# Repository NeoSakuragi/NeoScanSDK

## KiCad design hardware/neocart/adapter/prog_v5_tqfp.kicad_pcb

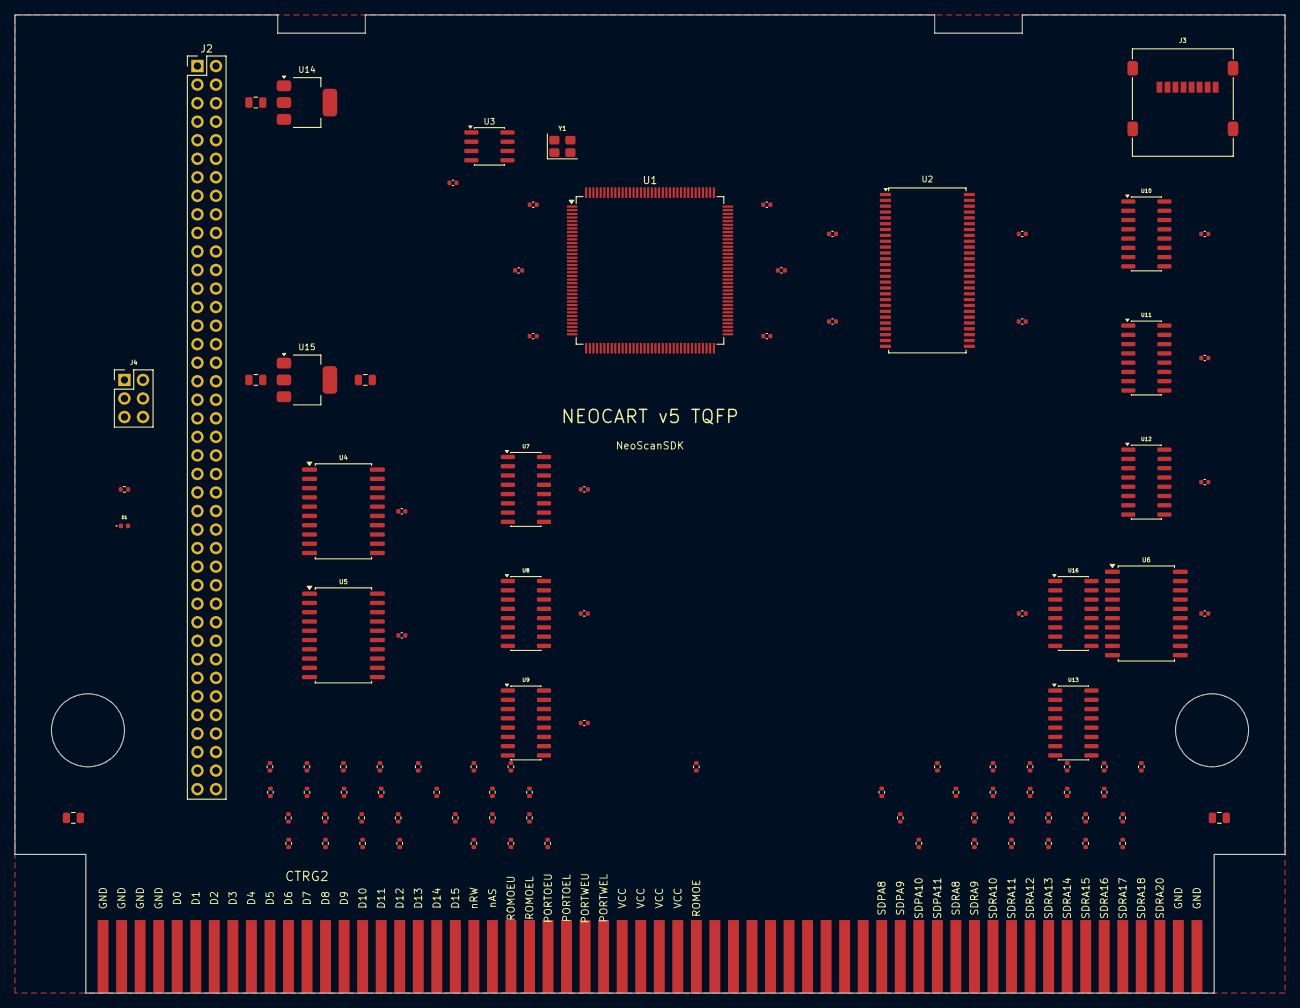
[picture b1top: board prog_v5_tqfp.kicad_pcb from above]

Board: 2 copper layers, 174.0 x 134.0 mm, 102 parts (0 on the bottom side), 241 nets, no tracks yet.

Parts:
C1, C2, C3, C4, C5, C6, C7, C8, C9, C10, C11, C12, C13, C14, C15, C16, C17, C18, C19, C20, C21: 100nF; C_0402_1005Metric
C22, C23, C24, C25, C26: 10uF; C_0805_2012Metric
CTRG2: MVS_PROG
D1: LED; LED_0402_1005Metric
J2: TO_CHA; PinHeader_2x40_P2.54mm_Vertical
J3: microSD; microSD_HC_Molex_47219-2001
J4: JTAG; PinHeader_2x03_P2.54mm_Vertical
R1, R2, R3, R4, R5, R6, R7, R8, R9, R10, R11, R12, R13, R14, R15, R16, R17, R18, R19, R20, R21, R22, R23, R24, R25, R26, R27, R28, R29, R30, R31, R32, R33, R34, R35, R36, R37, R38, R39, R40, R41, R42, R43, R44, R45, R46, R47, R48, R49, R50, R51, R52, R53: 470R; R_0402_1005Metric
R54: 1K; R_0402_1005Metric
U1: LFE5U-25F; TQFP-144_20x20mm_P0.5mm
U2: W9825G6KH; TSOP-II-54_22.2x10.16mm_P0.8mm
U3: W25Q32; SOIC-8_3.9x4.9mm_P1.27mm
U4, U5, U6: 74LVC245; SOIC-20W_7.5x12.8mm_P1.27mm
U7, U8, U9, U10, U11, U12, U13: 74HC165; SOIC-16_3.9x9.9mm_P1.27mm
U14: AMS1117-3.3; SOT-223-3_TabPin2
U15: AMS1117-1.2; SOT-223-3_TabPin2
U16: 74HC595; SOIC-16_3.9x9.9mm_P1.27mm
Y1: 50MHz; Crystal_SMD_3225-4Pin_3.2x2.5mm

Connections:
68KCLK: CTRG2.B24, R25.1
A1: CTRG2.B5, R1.1
A1_R: R1.2, U7.7
A2: CTRG2.B6, R2.1
A2_R: R2.2, U7.6
A3: CTRG2.B7, R3.1
A3_R: R3.2, U7.5
A4: CTRG2.B8, R4.1
A4_R: R4.2, U7.4
A5: CTRG2.B9, R5.1
A5_R: R5.2, U7.3
A6: CTRG2.B10, R6.1
A6_R: R6.2, U7.13
A7: CTRG2.B11, R7.1
A7_R: R7.2, U7.12
A8: CTRG2.B12, R8.1
A8_R: R8.2, U7.11
A9: CTRG2.B13, R9.1
A9_R: R9.2, U8.7
A10: CTRG2.B14, R10.1
A10_R: R10.2, U8.6
A11: CTRG2.B15, R11.1
A11_R: R11.2, U8.5
A12: CTRG2.B16, R12.1
A12_R: R12.2, U8.4
A13: CTRG2.B17, R13.1
A13_R: R13.2, U8.3
A14: CTRG2.B18, R14.1
A14_R: R14.2, U8.13
A15: CTRG2.B19, R15.1
A15_R: R15.2, U8.12
A16: CTRG2.B20, R16.1
A16_R: R16.2, U8.11
A17: CTRG2.B21, R17.1
A17_R: R17.2, U9.7
A18: CTRG2.B22, R18.1
A18_R: R18.2, U9.6
A19: CTRG2.B23, R19.1
A19_R: R19.2, U9.5
BUF_OE: U1.124, U4.19, U5.19
BUS_DIR: U1.121, U4.1, U5.1
CHA_CA4: J2.24, U1.12
CLK24M: J2.23, U1.3
CLK68K_DIV: R25.2, R26.1
CLK_C: J2.10, U1.116
CLK_CR: J2.16, U1.5
CLK_S: J2.13, U1.119
CLK_SF: J2.19, U1.10
CLK_SOUT: U1.49, U16.11
CLK_SR: U1.133, U7.2, U8.2, U9.2, U10.2, U11.2, U12.2, U13.2
D0: CTRG2.A5, U4.2
D1: CTRG2.A6, U4.3
D2: CTRG2.A7, U4.4
D3: CTRG2.A8, U4.5
D4: CTRG2.A9, U4.6
D5: CTRG2.A10, U4.7
D6: CTRG2.A11, U4.8
D7: CTRG2.A12, U4.9
D8: CTRG2.A13, U5.2
D9: CTRG2.A14, U5.3
D10: CTRG2.A15, U5.4
D11: CTRG2.A16, U5.5
D12: CTRG2.A17, U5.6
D13: CTRG2.A18, U5.7
D14: CTRG2.A19, U5.8
D15: CTRG2.A20, U5.9
FD0: U1.18, U4.18
FD1: U1.19, U4.17
FD2: U1.22, U4.16
FD3: U1.23, U4.15
FD4: U1.24, U4.14
FD5: U1.25, U4.13
FD6: U1.26, U4.12
FD7: U1.27, U4.11
FD8: U1.28, U5.18
FD9: U1.30, U5.17
FD10: U1.31, U5.16
FD11: U1.33, U5.15
FD12: U1.34, U5.14
FD13: U1.35, U5.13
FD14: U1.37, U5.12
FD15: U1.140, U5.11
FLASH_CLK: U1.54, U3.6
FLASH_CS: U1.48, U3.1
FLASH_MISO: U1.46, U3.2
FLASH_MOSI: U1.47, U3.5
FSD0: U6.2, U16.15
FSD1: U6.3, U16.1
FSD2: U6.4, U16.2
FSD3: U6.5, U16.3
FSD4: U6.6, U16.4
FSD5: U6.7, U16.5
FSD6: U6.8, U16.6
FSD7: U6.9, U16.7
GND: C1.2, C2.2, C3.2, C4.2, C5.2, C6.2, C7.2, C8.2, C9.2, C10.2, C11.2, C12.2, C13.2, C14.2, C15.2, C16.2, C17.2, C18.2, C19.2, C20.2, C21.2, C22.2, C23.2, C24.2, C25.2, C26.2, CTRG2.A1, CTRG2.A2, CTRG2.A3, CTRG2.A4, CTRG2.A59, CTRG2.A60, CTRG2.B1, CTRG2.B2, CTRG2.B3, CTRG2.B4, CTRG2.B26, CTRG2.B27, CTRG2.B59, CTRG2.B60, D1.2, J2.5, J2.6, J2.7, J2.8, J2.29, J2.30, J2.31, J2.32, J2.33, J2.34, J2.35, J2.36, J2.37, J2.38, J2.39, J2.40, J2.41, J2.42, J2.43, J2.44, J2.45, J2.46, J2.47, J2.48, J2.49, J2.50, J2.51, J2.52, J2.53, J2.54, J2.55, J2.56, J2.57, J2.58, J2.59, J2.60, J2.61, J2.62, J2.63, J2.64, J2.65, J2.66, J2.67, J2.68, J2.69, J2.70, J2.71, J2.72, J2.73, J2.74, J2.75, J2.76, J2.77, J2.78, J2.79, J2.80, J3.3, J3.6, J3.9, J4.6, R26.2, U1.8, U1.15, U1.21, U1.32, U1.42, U1.65, U1.75, U1.85, U1.87, U1.101, U1.123, U1.129, U1.131, U1.138, U2.3, U2.6, U2.9, U2.12, U2.39, U2.43, U2.46, U2.49, U2.52, U3.4, U4.10, U5.10, U6.10, U6.19, U7.8, U7.10, U7.14, U8.8, U8.14, U9.8, U9.14, U10.8, U10.10, U10.14, U11.8, U11.14, U12.8, U12.14, U13.3, U13.4, U13.8, U13.11, U13.12, U13.13, U13.14, U14.1, U15.1, U16.8, U16.13, Y1.3
JTAG_TCK: J4.3, U1.63
JTAG_TDI: J4.5, U1.61
JTAG_TDO: J4.4, U1.60
JTAG_TMS: J4.2, U1.64
LATCH_CR: J2.17, U1.6
LATCH_SF: J2.20, U1.11
LATCH_SOUT: U1.50, U16.12
LED1: D1.1, R54.1, U1.51
LOAD_C: J2.11, U1.117
LOAD_S: J2.14, U1.120
LOAD_SR: U1.134, U7.1, U8.1, U9.1, U10.1, U11.1, U12.1, U13.1
PCK1B: J2.21, U1.1
PCK2B: J2.22, U1.2
RESET_CHA: J2.27, U1.126
ROMOE: CTRG2.A33, R24.1
ROMOEL: CTRG2.A24, R23.1
ROMOEL_R: R23.2, U9.12
ROMOEU: CTRG2.A23, R22.1
ROMOEU_R: R22.2, U9.13
ROMOE_R: R24.2, U9.11
SDMRD: CTRG2.B58, R52.1
SDMRD_CHA: J2.25, U1.13
SDMRD_R: R52.2, U13.6
SDPA8: CTRG2.A43, R48.1
SDPA8_R: R48.2, U12.13
SDPA9: CTRG2.A44, R49.1
SDPA9_R: R49.2, U12.12
SDPA10: CTRG2.A45, R50.1
SDPA10_R: R50.2, U12.11
SDPA11: CTRG2.A46, R51.1
SDPA11_R: R51.2, U13.7
SDPAD0: CTRG2.B40, U6.18
SDPAD1: CTRG2.B41, U6.17
SDPAD2: CTRG2.B42, U6.16
SDPAD3: CTRG2.B43, U6.15
SDPAD4: CTRG2.B44, U6.14
SDPAD5: CTRG2.B45, U6.13
SDPAD6: CTRG2.B46, U6.12
SDPAD7: CTRG2.B47, U6.11
SDRA0: CTRG2.B48, R27.1
SDRA0_R: R27.2, U10.7
SDRA1: CTRG2.B49, R28.1
SDRA1_R: R28.2, U10.6
SDRA2: CTRG2.B50, R29.1
SDRA2_R: R29.2, U10.5
SDRA3: CTRG2.B51, R30.1
SDRA3_R: R30.2, U10.4
SDRA4: CTRG2.B52, R31.1
SDRA4_R: R31.2, U10.3
SDRA5: CTRG2.B53, R32.1
SDRA5_R: R32.2, U10.13
SDRA6: CTRG2.B54, R33.1
SDRA6_R: R33.2, U10.12
SDRA7: CTRG2.B55, R34.1
SDRA7_R: R34.2, U10.11
SDRA8: CTRG2.A47, R35.1
SDRA8_R: R35.2, U11.7
SDRA9: CTRG2.A48, R36.1
SDRA9_R: R36.2, U11.6
SDRA10: CTRG2.A49, R37.1
SDRA10_R: R37.2, U11.5
SDRA11: CTRG2.A50, R38.1
SDRA11_R: R38.2, U11.4
SDRA12: CTRG2.A51, R39.1
SDRA12_R: R39.2, U11.3
SDRA13: CTRG2.A52, R40.1
SDRA13_R: R40.2, U11.13
SDRA14: CTRG2.A53, R41.1
SDRA14_R: R41.2, U11.12
SDRA15: CTRG2.A54, R42.1
SDRA15_R: R42.2, U11.11
SDRA16: CTRG2.A55, R43.1
SDRA16_R: R43.2, U12.7
SDRA17: CTRG2.A56, R44.1
SDRA17_R: R44.2, U12.6
SDRA18: CTRG2.A57, R45.1
SDRA18_R: R45.2, U12.5
SDRA19: CTRG2.B57, R46.1
SDRA19_R: R46.2, U12.4
SDRA20: CTRG2.A58, R47.1
SDRA20_R: R47.2, U12.3
SDRAM_A0: U1.67, U2.23
SDRAM_A1: U1.68, U2.24
SDRAM_A2: U1.69, U2.25
SDRAM_A3: U1.71, U2.26
SDRAM_A4: U1.72, U2.29
SDRAM_A5: U1.73, U2.30
SDRAM_A6: U1.74, U2.31
SDRAM_A7: U1.76, U2.32
SDRAM_A8: U1.77, U2.33
SDRAM_A9: U1.78, U2.34
SDRAM_A10: U1.79, U2.22
SDRAM_A11: U1.80, U2.35
SDRAM_A12: U1.81, U2.36
SDRAM_BA0: U1.82, U2.20
SDRAM_BA1: U1.84, U2.21
SDRAM_CAS: U1.113, U2.17
SDRAM_CKE: U1.110, U2.37
SDRAM_CLK: U1.107, U2.38
SDRAM_CS: U1.111, U2.19
SDRAM_D0: U1.88, U2.2
SDRAM_D1: U1.89, U2.4
SDRAM_D2: U1.90, U2.5
SDRAM_D3: U1.91, U2.7
SDRAM_D4: U1.92, U2.8
SDRAM_D5: U1.93, U2.10
SDRAM_D6: U1.94, U2.11
SDRAM_D7: U1.95, U2.13
SDRAM_D8: U1.97, U2.42
SDRAM_D9: U1.98, U2.44
SDRAM_D10: U1.99, U2.45
SDRAM_D11: U1.102, U2.47
SDRAM_D12: U1.103, U2.48
SDRAM_D13: U1.104, U2.50
SDRAM_D14: U1.105, U2.51
SDRAM_D15: U1.106, U2.53
SDRAM_DQM: U1.108, U2.15
SDRAM_RAS: U1.112, U2.18
SDRAM_WE: U1.114, U2.16
SDROE: CTRG2.B56, R53.1
SDROE_R: R53.2, U13.5
SDROM: J2.26, U1.14
SD_CLK: J3.5, U1.40
SD_CS: J3.1, U1.39
SD_MISO: J3.7, U1.44
SD_MOSI: J3.2, U1.41
SER_C: J2.9, U1.115
SER_CR: J2.15, U1.4
SER_P: U1.125, U9.9
SER_S: J2.12, U1.118
SER_SD: U1.141, U13.9
SER_SF: J2.18, U1.7
SER_SOUT: U1.45, U16.14
SR1_OUT: U7.9, U8.10
SR2_OUT: U8.9, U9.10
SSR1_OUT: U10.9, U11.10
SSR2_OUT: U11.9, U12.10
SSR3_OUT: U12.9, U13.10
SYSTEMB: J2.28, U1.127
VCC_1V1: C1.1, C2.1, C3.1, C4.1, C25.1, U1.20, U1.29, U1.38, U1.66, U1.83, U1.130, U15.2
VCC_3V3: C5.1, C6.1, C7.1, C8.1, C9.1, C10.1, C11.1, C21.1, C23.1, C24.1, J2.1, J2.2, J3.4, J4.1, R54.2, U1.9, U1.16, U1.17, U1.36, U1.43, U1.53, U1.70, U1.86, U1.96, U1.100, U1.122, U1.132, U1.137, U2.1, U2.14, U2.27, U2.28, U2.40, U2.41, U2.54, U3.3, U3.7, U3.8, U14.2, U15.3, U16.10, U16.16
VCC_5V: C12.1, C13.1, C14.1, C15.1, C16.1, C17.1, C18.1, C19.1, C20.1, C22.1, C26.1, CTRG2.A29, CTRG2.A30, CTRG2.A31, CTRG2.A32, CTRG2.B29, CTRG2.B30, CTRG2.B31, CTRG2.B32, J2.3, J2.4, U4.20, U5.20, U6.1, U6.20, U7.16, U8.16, U9.16, U10.16, U11.16, U12.16, U13.16, U14.3
nAS: CTRG2.A22, R21.1
nAS_R: R21.2, U9.3
nRW: CTRG2.A21, R20.1
nRW_R: R20.2, U9.4

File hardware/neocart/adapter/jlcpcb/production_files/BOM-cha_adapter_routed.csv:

Comment,Designator,Footprint,LCSC,Quantity
100nF,"C1,C2,C3,C4,C5",C_0402_1005Metric,C1525,5
10uF,C6,C_0805_2012Metric,C15850,1
470R,"R1,R10,R11,R12,R13,R14,R15,R16,R17,R18,R19,R2,R20,R21,R22,R23,R24,R25,R26,R27,R28,R29,R3,R30,R31,R32,R33,R34,R35,R36,R37,R38,R39,R4,R40,R5,R6,R7,R8,R9",R_0402_1005Metric,C25900,40
74HC165,"U1,U2,U3,U4,U5",SOIC-16_3.9x9.9mm_P1.27mm,C5613,5
FROM_PROG,J2,PinHeader_2x40_P2.54mm_Vertical,C5224034,1

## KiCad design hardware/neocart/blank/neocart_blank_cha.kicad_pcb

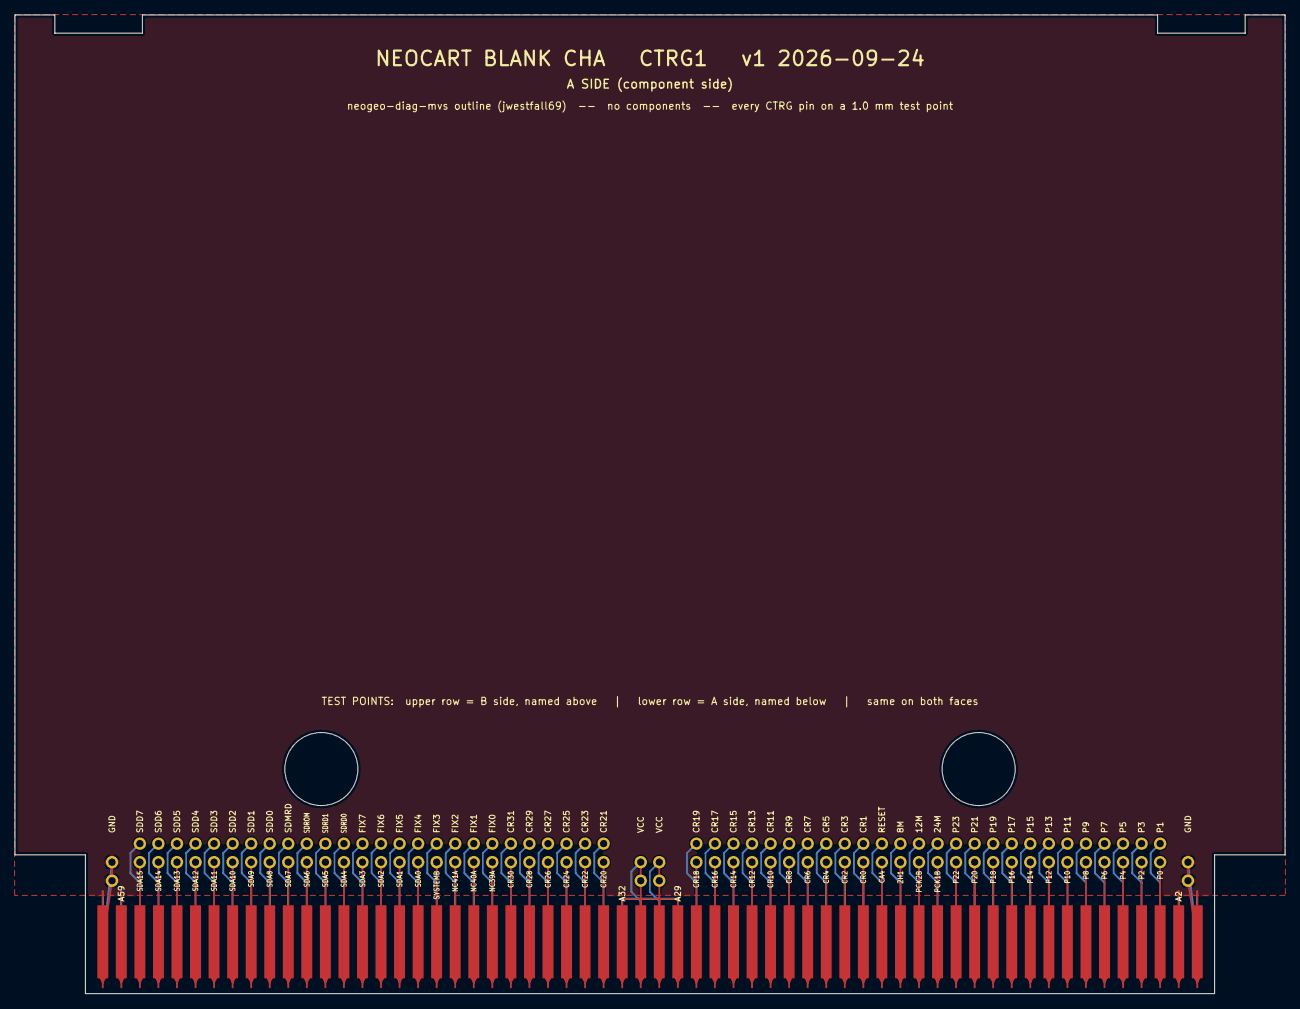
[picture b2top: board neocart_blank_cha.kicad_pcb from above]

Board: 2 copper layers, 173.9 x 134.0 mm, 4 parts (1 on the bottom side), 106 nets.

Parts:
J1: neogeo-mvs-cha-a-side-edge; neogeo-mvs-a-side-edge
J2: neogeo-mvs-cha-a-side-edge; neogeo-mvs-cha-edge-test-points
J3: neogeo-mvs-cha-b-side-edge; neogeo-mvs-cha-edge-test-points
J4: neogeo-mvs-cha-b-side-edge; neogeo-mvs-b-side-edge

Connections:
2H1: J1.17 (2H1), J2.17 (2H1)
8M: J3.17 (8M), J4.17 (8M)
12M: J3.16 (12M), J4.16 (12M)
24M: J3.15 (24M), J4.15 (24M)
CA4: J1.18 (CA4), J2.18 (CA4)
CR0: J1.19 (CR0), J2.19 (CR0)
CR1: J3.19 (CR1), J4.19 (CR1)
CR2: J1.20 (CR2), J2.20 (CR2)
CR3: J3.20 (CR3), J4.20 (CR3)
CR4: J1.21 (CR4), J2.21 (CR4)
CR5: J3.21 (CR5), J4.21 (CR5)
CR6: J1.22 (CR6), J2.22 (CR6)
CR7: J3.22 (CR7), J4.22 (CR7)
CR8: J1.23 (CR8), J2.23 (CR8)
CR9: J3.23 (CR9), J4.23 (CR9)
CR10: J1.24 (CR10), J2.24 (CR10)
CR11: J3.24 (CR11), J4.24 (CR11)
CR12: J1.25 (CR12), J2.25 (CR12)
CR13: J3.25 (CR13), J4.25 (CR13)
CR14: J1.26 (CR14), J2.26 (CR14)
CR15: J3.26 (CR15), J4.26 (CR15)
CR16: J1.27 (CR16), J2.27 (CR16)
CR17: J3.27 (CR17), J4.27 (CR17)
CR18: J1.28 (CR18), J2.28 (CR18)
CR19: J3.28 (CR19), J4.28 (CR19)
CR20: J1.33 (CR20), J2.33 (CR20)
CR21: J3.33 (CR21), J4.33 (CR21)
CR22: J1.34 (CR22), J2.34 (CR22)
CR23: J3.34 (CR23), J4.34 (CR23)
CR24: J1.35 (CR24), J2.35 (CR24)
CR25: J3.35 (CR25), J4.35 (CR25)
CR26: J1.36 (CR26), J2.36 (CR26)
CR27: J3.36 (CR27), J4.36 (CR27)
CR28: J1.37 (CR28), J2.37 (CR28)
CR29: J3.37 (CR29), J4.37 (CR29)
CR30: J1.38 (CR30), J2.38 (CR30)
CR31: J3.38 (CR31), J4.38 (CR31)
FIX0: J3.39 (FIXD0), J4.39 (FIXD0)
FIX1: J3.40 (FIXD1), J4.40 (FIXD1)
FIX2: J3.41 (FIXD2), J4.41 (FIXD2)
FIX3: J3.42 (FIXD3), J4.42 (FIXD3)
FIX4: J3.43 (FIXD4), J4.43 (FIXD4)
FIX5: J3.44 (FIXD5), J4.44 (FIXD5)
FIX6: J3.45 (FIXD6), J4.45 (FIXD6)
FIX7: J3.46 (FIXD7), J4.46 (FIXD7)
GND: J1.1 (GND), J1.2 (GND), J1.59 (GND), J1.60 (GND), J2.1 (GND), J2.60 (GND), J3.1 (GND), J3.60 (GND), J4.1 (GND), J4.2 (GND), J4.59 (GND), J4.60 (GND)
NC39A: J1.39 (NC), J2.39 (NC)
NC40A: J1.40 (NC), J2.40 (NC)
NC41A: J1.41 (NC), J2.41 (NC)
P0: J1.3 (P0), J2.3 (P0)
P1: J3.3 (P1), J4.3 (P1)
P2: J1.4 (P2), J2.4 (P2)
P3: J3.4 (P3), J4.4 (P3)
P4: J1.5 (P4), J2.5 (P4)
P5: J3.5, J4.5
P6: J1.6, J2.6
P7: J3.6 (P7), J4.6 (P7)
P8: J1.7 (P8), J2.7 (P8)
P9: J3.7 (P9), J4.7 (P9)
P10: J1.8 (P10), J2.8 (P10)
P11: J3.8 (P11), J4.8 (P11)
P12: J1.9 (P12), J2.9 (P12)
P13: J3.9 (P13), J4.9 (P13)
P14: J1.10 (P14), J2.10 (P14)
P15: J3.10 (P15), J4.10 (P15)
P16: J1.11 (P16), J2.11 (P16)
P17: J3.11 (P17), J4.11 (P17)
P18: J1.12 (P18), J2.12 (P18)
P19: J3.12 (P19), J4.12 (P19)
P20: J1.13 (P20), J2.13 (P20)
P21: J3.13 (P21), J4.13 (P21)
P22: J1.14 (P22), J2.14 (P22)
P23: J3.14 (P23), J4.14 (P23)
PCK1B: J1.15 (PCK1B), J2.15 (PCK1B)
PCK2B: J1.16 (PCK2B), J2.16 (PCK2B)
RESET: J3.18 (RESET), J4.18 (RESET)
SDA0: J1.43 (SDA0), J2.43 (SDA0)
SDA1: J1.44 (SDA1), J2.44 (SDA1)
SDA2: J1.45 (SDA2), J2.45 (SDA2)
SDA3: J1.46 (SDA3), J2.46 (SDA3)
SDA4: J1.47 (SDA4), J2.47 (SDA4)
SDA5: J1.48 (SDA5), J2.48 (SDA5)
SDA6: J1.49 (SDA6), J2.49 (SDA6)
SDA7: J1.50 (SDA7), J2.50 (SDA7)
SDA8: J1.51 (SDA8), J2.51 (SDA8)
SDA9: J1.52 (SDA9), J2.52 (SDA9)
SDA10: J1.53 (SDA10), J2.53 (SDA10)
SDA11: J1.54 (SDA11), J2.54 (SDA11)
SDA12: J1.55 (SDA12), J2.55 (SDA12)
SDA13: J1.56 (SDA13), J2.56 (SDA13)
SDA14: J1.57 (SDA14), J2.57 (SDA14)
SDA15: J1.58 (SDA15), J2.58 (SDA15)
SDD0: J3.51 (SDD0), J4.51 (SDD0)
SDD1: J3.52 (SDD1), J4.52 (SDD1)
SDD2: J3.53 (SDD2), J4.53 (SDD2)
SDD3: J3.54 (SDD3), J4.54 (SDD3)
SDD4: J3.55 (SDD4), J4.55 (SDD4)
SDD5: J3.56 (SDD5), J4.56 (SDD5)
SDD6: J3.57 (SDD6), J4.57 (SDD6)
SDD7: J3.58 (SDD7), J4.58 (SDD7)
SDMRD: J3.50 (SDMRD), J4.50 (SDMRD)
SDRD0: J3.47 (SDRD0), J4.47 (SDRD0)
SDRD1: J3.48 (SDRD1), J4.48 (SDRD1)
SDROM: J3.49 (SDROM), J4.49 (SDROM)
SYSTEMB: J1.42 (SLOTCS), J2.42 (SLOTCS)
VCC: J1.29 (VCC), J1.30 (VCC), J1.31 (VCC), J1.32 (VCC), J2.30 (VCC), J2.31 (VCC), J3.30 (VCC), J3.31 (VCC), J4.29 (VCC), J4.30 (VCC), J4.31 (VCC), J4.32 (VCC)

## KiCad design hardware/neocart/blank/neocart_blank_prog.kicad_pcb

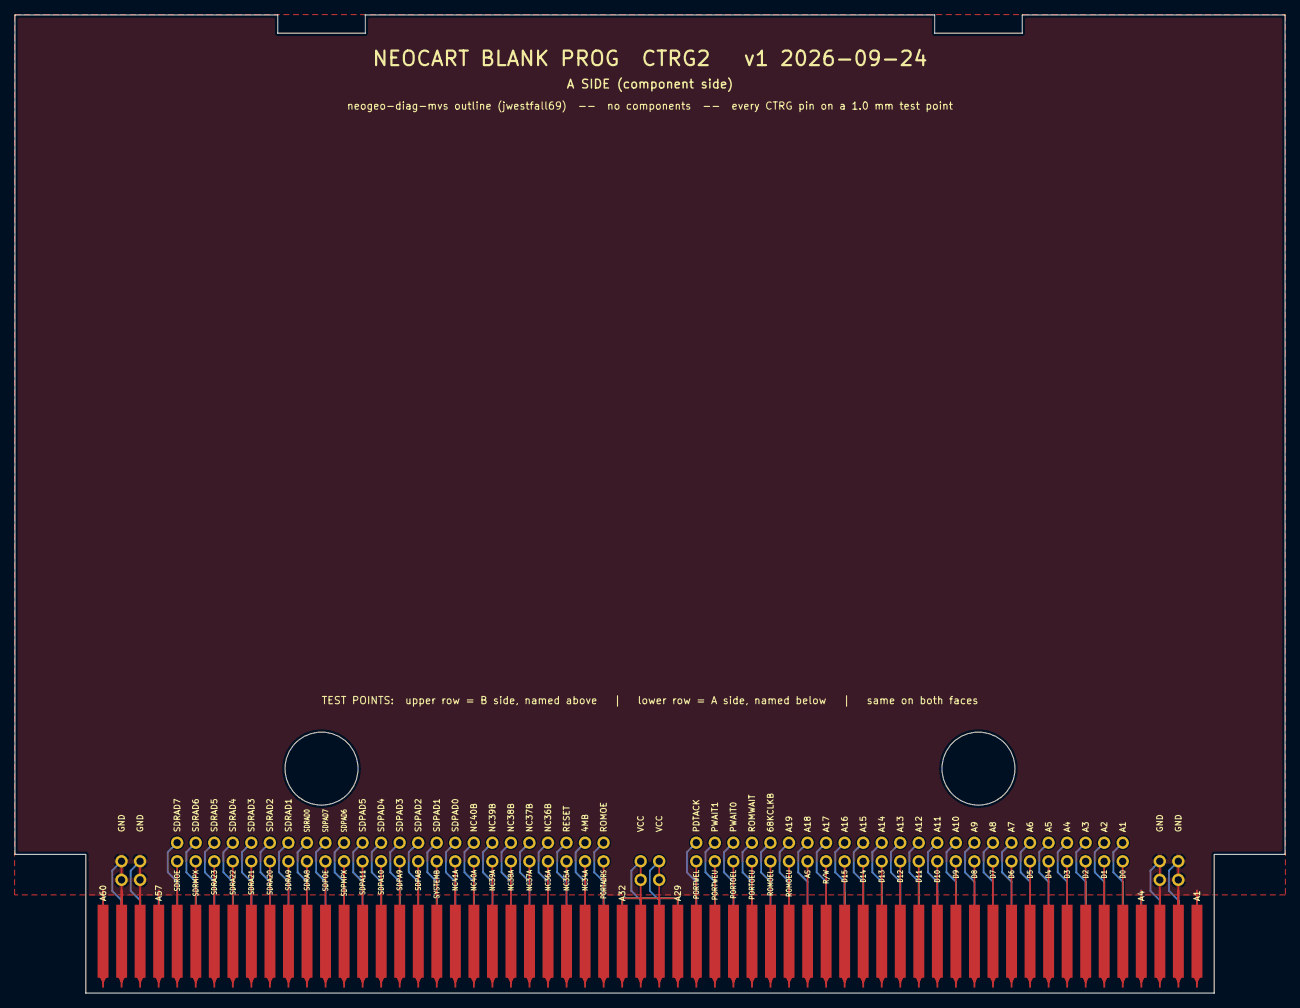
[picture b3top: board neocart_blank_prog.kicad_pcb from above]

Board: 2 copper layers, 174.0 x 134.0 mm, 4 parts (1 on the bottom side), 98 nets.

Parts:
J1: NeoGeo MVS Prog B Side Edge; neogeo-mvs-prog-b-side-edge
J2: NeoGeo MVS Prog A Side Edge; neogeo-mvs-prog-a-side-edge
J3: NeoGeo MVS Prog B Side Edge; neogeo-mvs-prog-edge-test-points
J4: NeoGeo MVS Prog A Side Edge; neogeo-mvs-prog-edge-test-points

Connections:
4MB: J1.34 (4MB), J3.34 (4MB)
68KCLKB: J1.24 (68KCLKB), J3.24 (68KCLKB)
A1: J1.5 (A1), J3.5 (A1)
A2: J1.6 (A2), J3.6 (A2)
A3: J1.7 (A3), J3.7 (A3)
A4: J1.8 (A4), J3.8 (A4)
A5: J1.9 (A5), J3.9 (A5)
A6: J1.10 (A6), J3.10 (A6)
A7: J1.11 (A7), J3.11 (A7)
A8: J1.12 (A8), J3.12 (A8)
A9: J1.13 (A9), J3.13 (A9)
A10: J1.14 (A10), J3.14 (A10)
A11: J1.15 (A11), J3.15 (A11)
A12: J1.16 (A12), J3.16 (A12)
A13: J1.17 (A13), J3.17 (A13)
A14: J1.18 (A14), J3.18 (A14)
A15: J1.19 (A15), J3.19 (A15)
A16: J1.20 (A16), J3.20 (A16)
A17: J1.21 (A17), J3.21 (A17)
A18: J1.22 (A18), J3.22 (A18)
A19: J1.23 (A19), J3.23 (A19)
AS: J2.22 (AS), J4.22 (AS)
D0: J2.5 (D0), J4.5 (D0)
D1: J2.6 (D1), J4.6 (D1)
D2: J2.7 (D2), J4.7 (D2)
D3: J2.8 (D3), J4.8 (D3)
D4: J2.9 (D4), J4.9 (D4)
D5: J2.10 (D5), J4.10 (D5)
D6: J2.11 (D6), J4.11 (D6)
D7: J2.12 (D7), J4.12 (D7)
D8: J2.13 (D8), J4.13 (D8)
D9: J2.14 (D9), J4.14 (D9)
D10: J2.15 (D10), J4.15 (D10)
D11: J2.16 (D11), J4.16 (D11)
D12: J2.17 (D12), J4.17 (D12)
D13: J2.18 (D13), J4.18 (D13)
D14: J2.19 (D14), J4.19 (D14)
D15: J2.20 (D15), J4.20 (D15)
GND: J1.1 (GND), J1.2 (GND), J1.3 (GND), J1.4 (GND), J1.57 (GND), J1.58 (GND), J1.59 (GND), J1.60 (GND), J2.1 (GND), J2.2 (GND), J2.3 (GND), J2.4 (GND), J2.57 (GND), J2.58 (GND), J2.59 (GND), J2.60 (GND), J3.2 (GND), J3.3 (GND), J3.58 (GND), J3.59 (GND), J4.2 (GND), J4.3 (GND), J4.58 (GND), J4.59 (GND)
NC34A: J2.34 (NC), J4.34 (NC)
NC35A: J2.35 (NC), J4.35 (NC)
NC36A: J2.36 (NC), J4.36 (NC)
NC36B: J1.36 (NC), J3.36 (NC)
NC37A: J2.37 (NC), J4.37 (NC)
NC37B: J1.37 (NC), J3.37 (NC)
NC38A: J2.38 (NC), J4.38 (NC)
NC38B: J1.38 (NC), J3.38 (NC)
NC39A: J2.39 (NC), J4.39 (NC)
NC39B: J1.39 (NC), J3.39 (NC)
NC40A: J2.40 (NC), J4.40 (NC)
NC40B: J1.40 (NC), J3.40 (NC)
NC41A: J2.41 (NC), J4.41 (NC)
PDTACK: J1.28 (PDTACK), J3.28 (PDTACK)
PORTADRS: J2.33 (PORTADRS), J4.33 (PORTADRS)
PORTOEL: J2.26 (PORTOEL), J4.26 (PORTOEL)
PORTOEU: J2.25 (PORTOEU), J4.25 (PORTOEU)
PORTWEL: J2.28 (PORTWEL), J4.28 (PORTWEL)
PORTWEU: J2.27 (PORTWEU), J4.27 (PORTWEU)
PWAIT0: J1.26 (PWAIT0), J3.26 (PWAIT0)
PWAIT1: J1.27 (PWAIT1), J3.27 (PWAIT1)
RESET: J1.35 (RESET), J3.35 (RESET)
ROMOE: J1.33 (ROMOE), J3.33 (ROMOE)
ROMOEL: J2.24 (ROMOEL), J4.24 (ROMOEL)
ROMOEU: J2.23 (ROMOEU), J4.23 (ROMOEU)
ROMWAIT: J1.25 (ROMWAIT), J3.25 (ROMWAIT)
R_W: J2.21 (R/W), J4.21 (R/W)
SDPA8: J2.43 (SDPA8), J4.43 (SDPA8)
SDPA9: J2.44 (SDPA9), J4.44 (SDPA9)
SDPA10: J2.45 (SDPA10), J4.45 (SDPA10)
SDPA11: J2.46 (SDPA11), J4.46 (SDPA11)
SDPAD0: J1.41 (SDPAD0), J3.41 (SDPAD0)
SDPAD1: J1.42 (SDPAD1), J3.42 (SDPAD1)
SDPAD2: J1.43 (SDPAD2), J3.43 (SDPAD2)
SDPAD3: J1.44 (SDPAD3), J3.44 (SDPAD3)
SDPAD4: J1.45 (SDPAD4), J3.45 (SDPAD4)
SDPAD5: J1.46 (SDPAD5), J3.46 (SDPAD5)
SDPAD6: J1.47 (SDPAD6), J3.47 (SDPAD6)
SDPAD7: J1.48 (SDPAD7), J3.48 (SDPAD7)
SDPMPX: J2.47 (SDPMPX), J4.47 (SDPMPX)
SDPOE: J2.48 (SDPOE), J4.48 (SDPOE)
SDRA8: J2.49 (SDRA8), J4.49 (SDRA8)
SDRA9: J2.50 (SDRA9), J4.50 (SDRA9)
SDRA20: J2.51 (SDRA20), J4.51 (SDRA20)
SDRA21: J2.52 (SDRA21), J4.52 (SDRA21)
SDRA22: J2.53 (SDRA22), J4.53 (SDRA22)
SDRA23: J2.54 (SDRA23), J4.54 (SDRA23)
SDRAD0: J1.49 (SDRAD0), J3.49 (SDRAD0)
SDRAD1: J1.50 (SDRAD1), J3.50 (SDRAD1)
SDRAD2: J1.51 (SDRAD2), J3.51 (SDRAD2)
SDRAD3: J1.52 (SDRAD3), J3.52 (SDRAD3)
SDRAD4: J1.53 (SDRAD4), J3.53 (SDRAD4)
SDRAD5: J1.54 (SDRAD5), J3.54 (SDRAD5)
SDRAD6: J1.55 (SDRAD6), J3.55 (SDRAD6)
SDRAD7: J1.56 (SDRAD7), J3.56 (SDRAD7)
SDRMPX: J2.55 (SDRMPX), J4.55 (SDRMPX)
SDROE: J2.56 (SDROE), J4.56 (SDROE)
SYSTEMB: J2.42 (SLOTCS), J4.42 (SLOTCS)
VCC: J1.29 (VCC), J1.30 (VCC), J1.31 (VCC), J1.32 (VCC), J2.29 (VCC), J2.30 (VCC), J2.31 (VCC), J2.32 (VCC), J3.30 (VCC), J3.31 (VCC), J4.30 (VCC), J4.31 (VCC)

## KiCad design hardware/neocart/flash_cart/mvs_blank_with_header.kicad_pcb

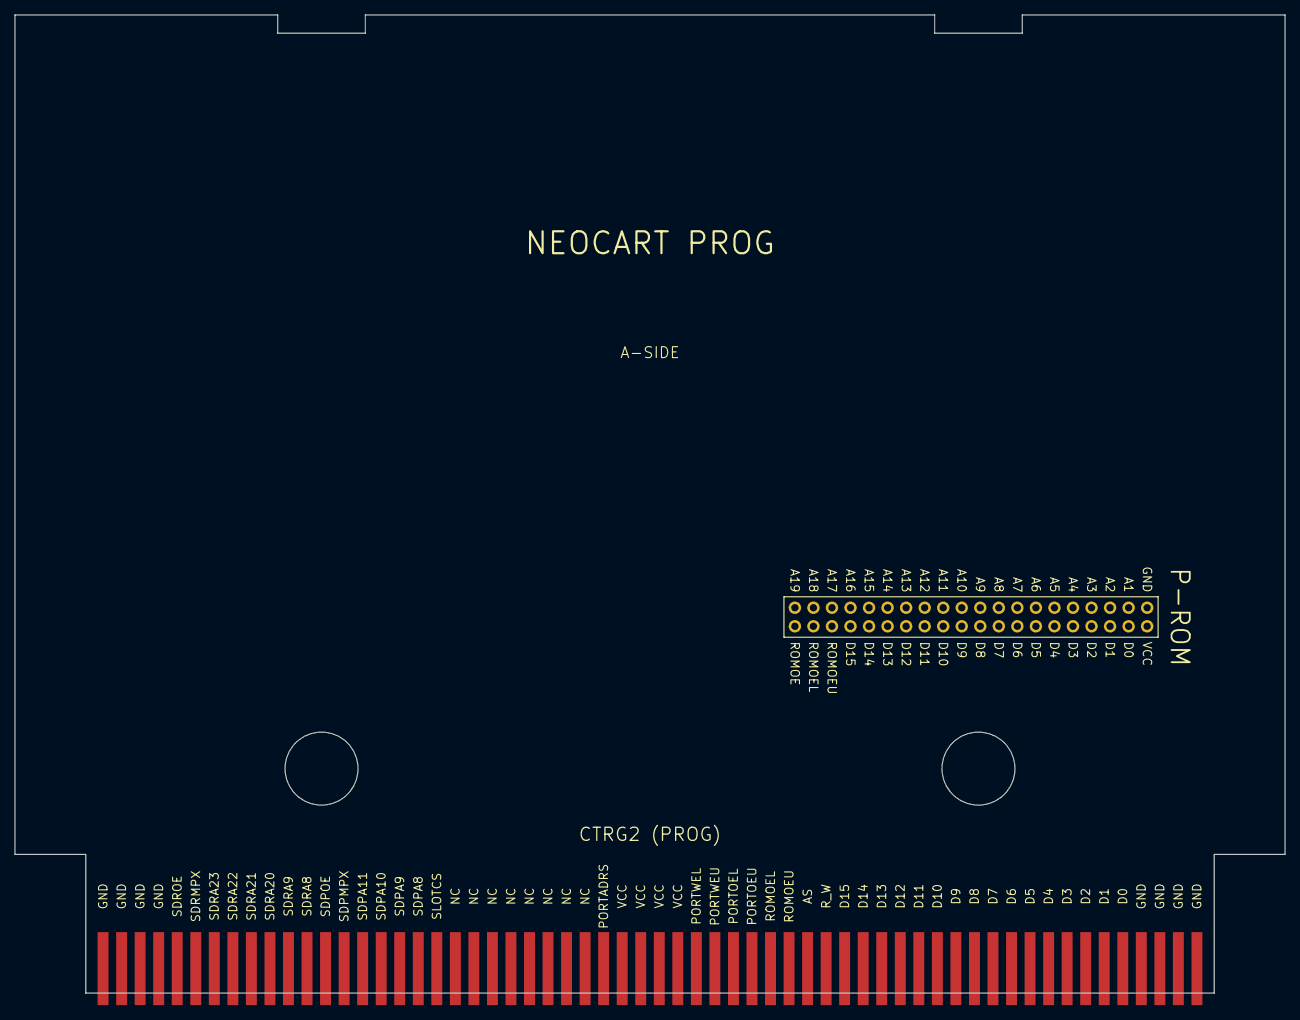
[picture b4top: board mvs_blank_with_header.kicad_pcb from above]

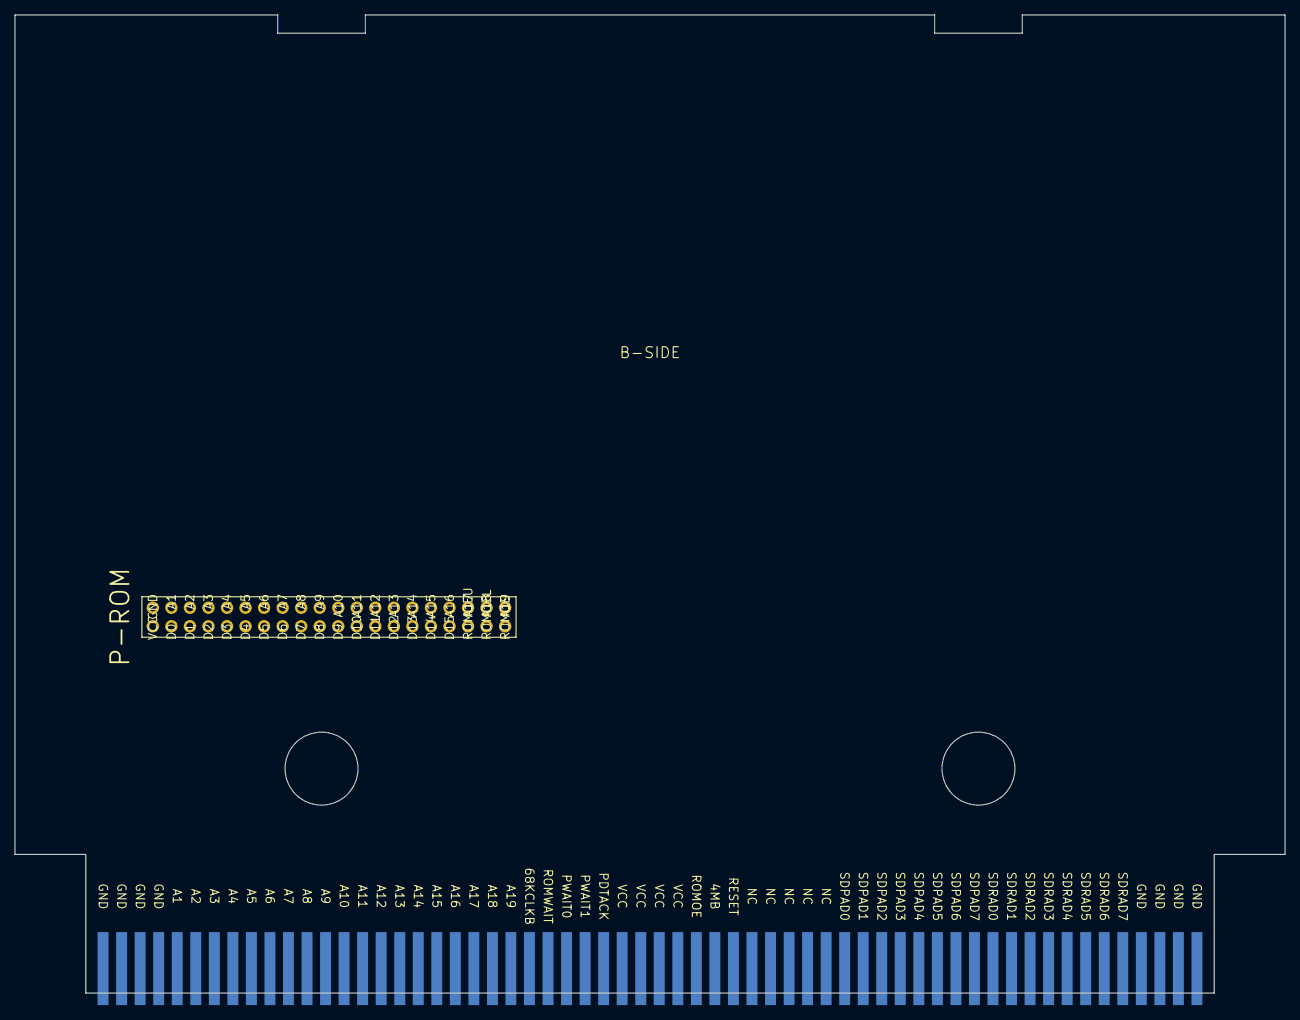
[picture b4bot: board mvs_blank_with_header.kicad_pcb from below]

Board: 2 copper layers, 174.0 x 134.0 mm, 121 parts (60 on the bottom side), 40 nets, no tracks yet.

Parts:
A1, A2, A3, A4, A57, A58, A59, A60: GND
A5: D0
A6: D1
A7: D2
A8: D3
A9: D4
A10: D5
A11: D6
A12: D7
A13: D8
A14: D9
A15: D10
A16: D11
A17: D12
A18: D13
A19: D14
A20: D15
A21: R_W
A22: AS
A23: ROMOEU
A24: ROMOEL
A25: PORTOEU
A26: PORTOEL
A27: PORTWEU
A28: PORTWEL
A29, A30, A31, A32: VCC
A33: PORTADRS
A34, A35, A36, A37, A38, A39, A40, A41: NC
A42: SLOTCS
A43: SDPA8
A44: SDPA9
A45: SDPA10
A46: SDPA11
A47: SDPMPX
A48: SDPOE
A49: SDRA8
A50: SDRA9
A51: SDRA20
A52: SDRA21
A53: SDRA22
A54: SDRA23
A55: SDRMPX
A56: SDROE
B1, B2, B3, B4, B57, B58, B59, B60: GND
B5: A1
B6: A2
B7: A3
B8: A4
B9: A5
B10: A6
B11: A7
B12: A8
B13: A9
B14: A10
B15: A11
B16: A12
B17: A13
B18: A14
B19: A15
B20: A16
B21: A17
B22: A18
B23: A19
B24: 68KCLKB
B25: ROMWAIT
B26: PWAIT0
B27: PWAIT1
B28: PDTACK
B29, B30, B31, B32: VCC
B33: ROMOE
B34: 4MB
B35: RESET
B36, B37, B38, B39, B40: NC
B41: SDPAD0
B42: SDPAD1
B43: SDPAD2
B44: SDPAD3
B45: SDPAD4
B46: SDPAD5
B47: SDPAD6
B48: SDPAD7
B49: SDRAD0
B50: SDRAD1
B51: SDRAD2
B52: SDRAD3
B53: SDRAD4
B54: SDRAD5
B55: SDRAD6
B56: SDRAD7
J_PROM: P-ROM 2x20

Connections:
A1: B5.1, J_PROM.3
A2: B6.1, J_PROM.5
A3: B7.1, J_PROM.7
A4: B8.1, J_PROM.9
A5: B9.1, J_PROM.11
A6: B10.1, J_PROM.13
A7: B11.1, J_PROM.15
A8: B12.1, J_PROM.17
A9: B13.1, J_PROM.19
A10: B14.1, J_PROM.21
A11: B15.1, J_PROM.23
A12: B16.1, J_PROM.25
A13: B17.1, J_PROM.27
A14: B18.1, J_PROM.29
A15: B19.1, J_PROM.31
A16: B20.1, J_PROM.33
A17: B21.1, J_PROM.35
A18: B22.1, J_PROM.37
A19: B23.1, J_PROM.39
D0: A5.1, J_PROM.4
D1: A6.1, J_PROM.6
D2: A7.1, J_PROM.8
D3: A8.1, J_PROM.10
D4: A9.1, J_PROM.12
D5: A10.1, J_PROM.14
D6: A11.1, J_PROM.16
D7: A12.1, J_PROM.18
D8: A13.1, J_PROM.20
D9: A14.1, J_PROM.22
D10: A15.1, J_PROM.24
D11: A16.1, J_PROM.26
D12: A17.1, J_PROM.28
D13: A18.1, J_PROM.30
D14: A19.1, J_PROM.32
D15: A20.1, J_PROM.34
GND: B1.1, J_PROM.1
ROMOE: B33.1, J_PROM.40
ROMOEL: A24.1, J_PROM.38
ROMOEU: A23.1, J_PROM.36
VCC: A29.1, J_PROM.2

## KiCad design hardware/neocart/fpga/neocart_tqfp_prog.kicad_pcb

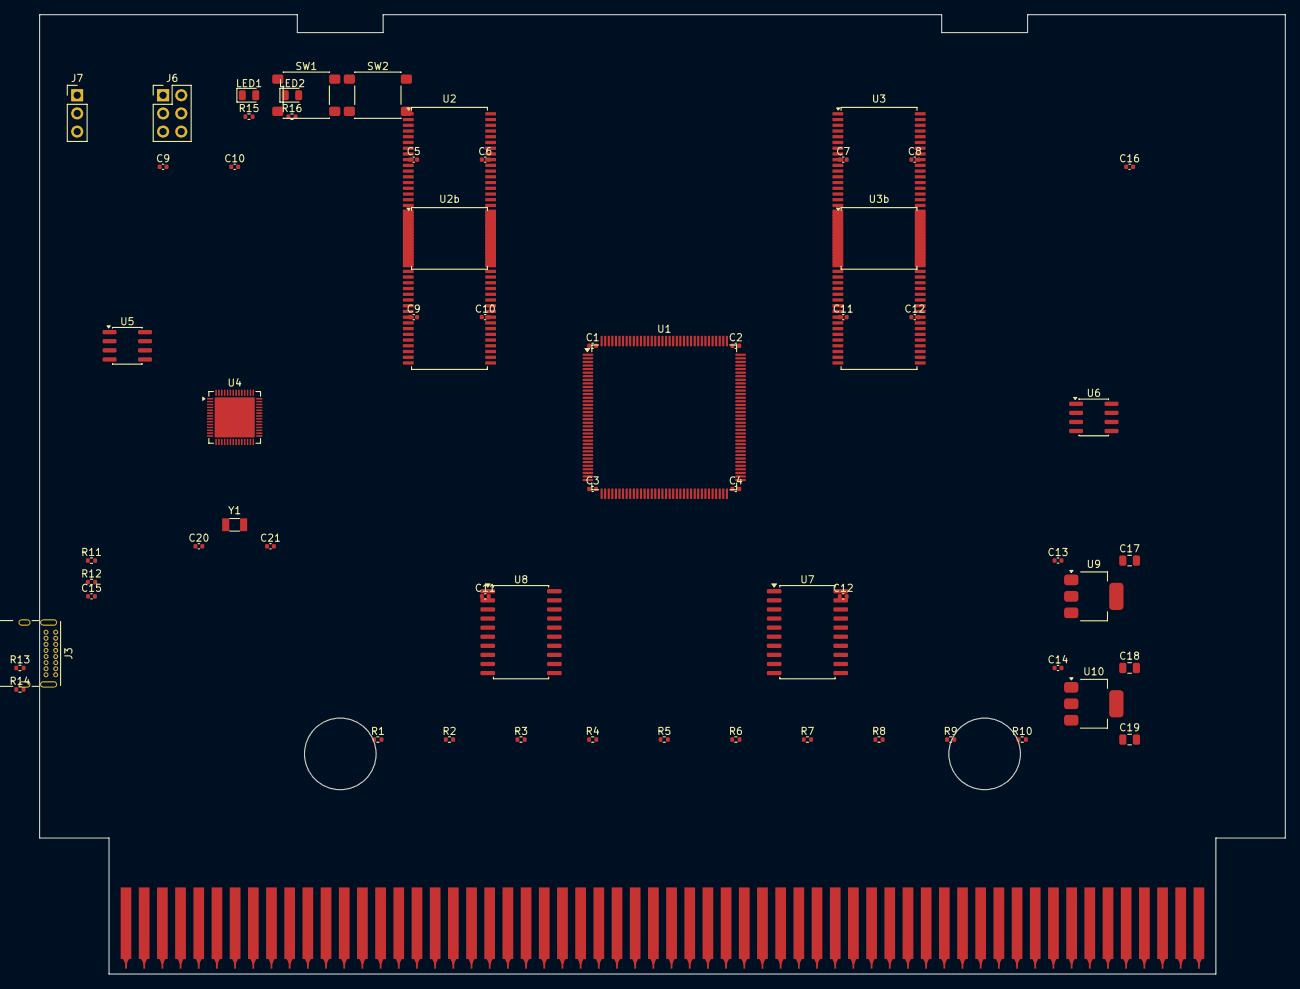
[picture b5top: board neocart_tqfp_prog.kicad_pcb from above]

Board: 4 copper layers, 174.0 x 134.0 mm, 63 parts (1 on the bottom side), 150 nets, no tracks yet.

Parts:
C1, C2, C3, C4, C5, C6, C7, C8, C9, C9#2, C10, C10#2, C11, C11#2, C12, C12#2, C13, C14, C15, C16, C20, C21: C_0402_1005Metric
C17, C18, C19: C_0805_2012Metric
J1: NeoGeo MVS Prog B Side Edge; neogeo-mvs-prog-b-side-edge
J2: NeoGeo MVS Prog A Side Edge; neogeo-mvs-prog-a-side-edge
J3: USB_C_Receptacle_GCT_USB4085
J6: PinHeader_2x03_P2.54mm_Vertical
J7: PinHeader_1x03_P2.54mm_Vertical
LED1, LED2: LED_0805_2012Metric
R1, R2, R3, R4, R5, R6, R7, R8, R9, R10, R11, R12, R13, R14, R15, R16: R_0402_1005Metric
SW1, SW2: SW_SPST_PTS645Sx43SMTR92
U1: TQFP-144_20x20mm_P0.5mm
U2, U2b, U3, U3b: TSOP-II-54_22.2x10.16mm_P0.8mm
U4: QFN-56-1EP_7x7mm_P0.4mm_EP5.6x5.6mm
U5, U6: SOIC-8_3.9x4.9mm_P1.27mm
U7, U8: SOIC-20W_7.5x12.8mm_P1.27mm
U9, U10: SOT-223-3_TabPin2
Y1: Crystal_SMD_3215-2Pin_3.2x1.5mm

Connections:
CFG_CS: U1.118, U6.1
CFG_MISO: U1.116, U6.2
CFG_MOSI: U1.115, U6.5
CFG_SCK: U1.117, U6.6
FPGA_PD0: U1.1, U7.18
FPGA_PD1: U1.2, U7.17
FPGA_PD2: U1.3, U7.16
FPGA_PD3: U1.4, U7.15
FPGA_PD4: U1.5, U7.14
FPGA_PD5: U1.6, U7.13
FPGA_PD6: U1.7, U7.12
FPGA_PD7: U1.8, U7.11
FPGA_PD8: U1.9, U8.18
FPGA_PD9: U1.10, U8.17
FPGA_PD10: U1.11, U8.16
FPGA_PD11: U1.12, U8.15
FPGA_PD12: U1.13, U8.14
FPGA_PD13: U1.14, U8.13
FPGA_PD14: U1.15, U8.12
FPGA_PD15: U1.16, U8.11
JTAG_TCK: J6.1, U1.122
JTAG_TDI: J6.3, U1.119
JTAG_TDO: J6.5, U1.120
JTAG_TMS: J6.4, U1.121
LED1_NET: LED1.1, R15.1, U1.99
LED2_NET: LED2.1, R16.1, U1.100
MA0: J1.48 (SDPAD7), U1.131
MA1: J1.49 (SDRAD0), U1.132
MA2: J1.50 (SDRAD1), U1.133
MA3: J1.51 (SDRAD2), U1.134
MA4: J1.52 (SDRAD3), U1.135
MA5: J1.53 (SDRAD4), U1.136
MA6: J1.54 (SDRAD5), U1.137
MA7: J1.55 (SDRAD6), U1.138
MA8: J2.47 (SDPMPX), U1.91
MA9: J2.48 (SDPOE), U1.92
MA10: J2.49 (SDRA8), U1.93
MA11: J2.50 (SDRA9), U1.94
MA12: J2.51 (SDRA20), U1.95
MA13: J2.52 (SDRA21), U1.96
MA14: J2.53 (SDRA22), U1.97
MA15: J2.54 (SDRA23), U1.98
MD0: J1.40 (NC), U1.123
MD1: J1.41 (SDPAD0), U1.124
MD2: J1.42 (SDPAD1), U1.125
MD3: J1.43 (SDPAD2), U1.126
MD4: J1.44 (SDPAD3), U1.127
MD5: J1.45 (SDPAD4), U1.128
MD6: J1.46 (SDPAD5), U1.129
MD7: J1.47 (SDPAD6), U1.130
PA0: J1.5 (A1), U1.17
PA1: J1.6 (A2), U1.18
PA2: J1.7 (A3), U1.19
PA3: J1.8 (A4), U1.20
PA4: J1.9 (A5), U1.21
PA5: J1.10 (A6), U1.22
PA6: J1.11 (A7), U1.23
PA7: J1.12 (A8), U1.24
PA8: J1.13 (A9), U1.25
PA9: J1.14 (A10), U1.26
PA10: J1.15 (A11), U1.27
PA11: J1.16 (A12), U1.28
PA12: J1.17 (A13), U1.29
PA13: J1.18 (A14), U1.30
PA14: J1.19 (A15), U1.31
PA15: J1.20 (A16), U1.32
PA16: J1.21 (A17), U1.33
PA17: J1.22 (A18), U1.34
PD0: J2.5 (D0), U7.2
PD1: J2.6 (D1), U7.3
PD2: J2.7 (D2), U7.4
PD3: J2.8 (D3), U7.5
PD4: J2.9 (D4), U7.6
PD5: J2.10 (D5), U7.7
PD6: J2.11 (D6), U7.8
PD7: J2.12 (D7), U7.9
PD8: J2.13 (D8), U8.2
PD9: J2.14 (D9), U8.3
PD10: J2.15 (D10), U8.4
PD11: J2.16 (D11), U8.5
PD12: J2.17 (D12), U8.6
PD13: J2.18 (D13), U8.7
PD14: J2.19 (D14), U8.8
PD15: J2.20 (D15), U8.9
QSPI_CS: U1.141, U4.56, U5.1
QSPI_SCK: U1.142, U4.53, U5.6
QSPI_SD0: U1.143, U4.51, U5.5
QSPI_SD1: U1.144, U4.52, U5.2
QSPI_SD2: U4.54, U5.3
QSPI_SD3: U4.55, U5.7
ROMOE: J2.33 (PORTADRS), U1.35
ROMOEL: J2.24 (ROMOEL), U1.89
ROMOEU: J2.23 (ROMOEU), U1.88
SDRAM_A0: U1.53, U2.44, U2b.44, U3.44, U3b.44
SDRAM_A1: U1.54, U2.45, U2b.45, U3.45, U3b.45
SDRAM_A2: U1.55, U2.46, U2b.46, U3.46, U3b.46
SDRAM_A3: U1.56, U2.47, U2b.47, U3.47, U3b.47
SDRAM_A4: U1.57, U2.48, U2b.48, U3.48, U3b.48
SDRAM_A5: U1.58, U2.49, U2b.49, U3.49, U3b.49
SDRAM_A6: U1.59, U2.50, U2b.50, U3.50, U3b.50
SDRAM_A7: U1.60, U2.51, U2b.51, U3.51, U3b.51
SDRAM_A8: U1.61, U2.52, U2b.52, U3.52, U3b.52
SDRAM_A9: U1.62, U2.53, U2b.53, U3.53, U3b.53
SDRAM_A10: U1.63, U2.54, U2b.54, U3.54, U3b.54
SDRAM_A11: U1.64, U2.1, U2b.1, U3.1, U3b.1
SDRAM_A12: U1.65, U2.2, U2b.2, U3.2, U3b.2
SDRAM_BA0: U1.66, U2.5, U2b.5, U3.5, U3b.5
SDRAM_BA1: U1.67, U2.6, U2b.6, U3.6, U3b.6
SDRAM_CASN: U1.69, U2.8, U2b.8, U3.8, U3b.8
SDRAM_CKE: U1.72, U2.10, U2b.10, U3.10, U3b.10
SDRAM_CLK: U1.71, U2.11, U2b.11, U3.11, U3b.11
SDRAM_CS0N: U1.73, U2.12
SDRAM_CS1N: U1.74, U3.12
SDRAM_CS2N: U1.75, U2b.12
SDRAM_CS3N: U1.76, U3b.12
SDRAM_DQ0: U1.37, U2.20, U2b.20, U3.20, U3b.20
SDRAM_DQ1: U1.38, U2.21, U2b.21, U3.21, U3b.21
SDRAM_DQ2: U1.39, U2.22, U2b.22, U3.22, U3b.22
SDRAM_DQ3: U1.40, U2.23, U2b.23, U3.23, U3b.23
SDRAM_DQ4: U1.41, U2.24, U2b.24, U3.24, U3b.24
SDRAM_DQ5: U1.42, U2.25, U2b.25, U3.25, U3b.25
SDRAM_DQ6: U1.43, U2.26, U2b.26, U3.26, U3b.26
SDRAM_DQ7: U1.44, U2.27, U2b.27, U3.27, U3b.27
SDRAM_DQ8: U1.45, U2.33, U2b.33, U3.33, U3b.33
SDRAM_DQ9: U1.46, U2.34, U2b.34, U3.34, U3b.34
SDRAM_DQ10: U1.47, U2.35, U2b.35, U3.35, U3b.35
SDRAM_DQ11: U1.48, U2.36, U2b.36, U3.36, U3b.36
SDRAM_DQ12: U1.49, U2.37, U2b.37, U3.37, U3b.37
SDRAM_DQ13: U1.50, U2.38, U2b.38, U3.38, U3b.38
SDRAM_DQ14: U1.51, U2.39, U2b.39, U3.39, U3b.39
SDRAM_DQ15: U1.52, U2.40, U2b.40, U3.40, U3b.40
SDRAM_DQMH: U1.78, U2.32, U2b.32, U3.32, U3b.32
SDRAM_DQML: U1.77, U2.18, U2b.18, U3.18, U3b.18
SDRAM_RASN: U1.68, U2.7, U2b.7, U3.7, U3b.7
SDRAM_WEN: U1.70, U2.9, U2b.9, U3.9, U3b.9
SDROE: J2.56 (SDROE), U1.87
SPI_CS: U1.112, U4.5
SPI_MISO: U1.110, U4.3
SPI_MOSI: U1.109, U4.2
SPI_SCK: U1.111, U4.4
USB_CC1: J3.A5, R13.1
USB_CC2: J3.B5, R14.1
USB_DM: J3.A7, J3.B7, R12.1, R12.2, U4.47
USB_DP: J3.A6, J3.B6, R11.1, R11.2, U4.46
USB_VBUS: J3.A4, J3.A9, J3.B4, J3.B9
VCC_1V1: U4.23, U4.50, U10.2
VCC_5V: J1.29 (VCC), J1.30 (VCC), J1.31 (VCC), J1.32 (VCC), J2.29 (VCC), J2.30 (VCC), J2.31 (VCC), J2.32 (VCC), U9.3
XTAL_IN: C20.1, U1.139, U4.20, Y1.1
XTAL_OUT: C21.1, U1.140, U4.21, Y1.2
nRW: J2.21 (R/W), U1.90
